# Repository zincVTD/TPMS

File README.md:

# Tire Pressure Monitoring System
Đây là mã nguồn firmware của đề tài TPMS của Võ Thành Danh. Dự án này thiết kế và phát triển một hệ thống mô phỏng hoạt động của ECU TPMS - một ECU có chức năng theo dõi tình trạng áp suất lốp xe trong các xe ô tô. Dự án thực hiện ECU TPMS trực tiếp, tức là sẽ có các cảm biến được gắn trực tiếp vào bên trong các bánh xe. Dữ liệu áp suất thu được sẽ được phát không dây ra bên ngoài và sẽ được thu bởi một bộ nhận trung tâm được đặt trong thân xe. Bộ nhận này sẽ xử lý thông tin nhận được và gửi dữ liệu ra ECU màn hình.
### Chi tiết các thành phần của dự án như sau:
- ADC_BLE: chứa mã nguồn firmware của ESP32C6 dùng để đọc giá trị cảm biến và gửi nó thông qua BLE.
- BLE_SPI: chứa mã nguồn firmware của ESP32C6 dùng để nhận dữ liệu từ BLE và gửi dữ liệu cho STM32 bằng SPI.
- TPMS: chứa mã nguồn firmware của STM32 dùng để nhận dữ liệu từ SPI và gửi nó cho ECU màn hình bằng CAN.
- Monitor: chứa mã nguồn firmware của STM32 dùng để nhận dữ liệu từ CAN và hiển thị chúng ra màn hình OLED SSD1306.\
\
**Video demo: https://youtu.be/x6ECv--hoa8**

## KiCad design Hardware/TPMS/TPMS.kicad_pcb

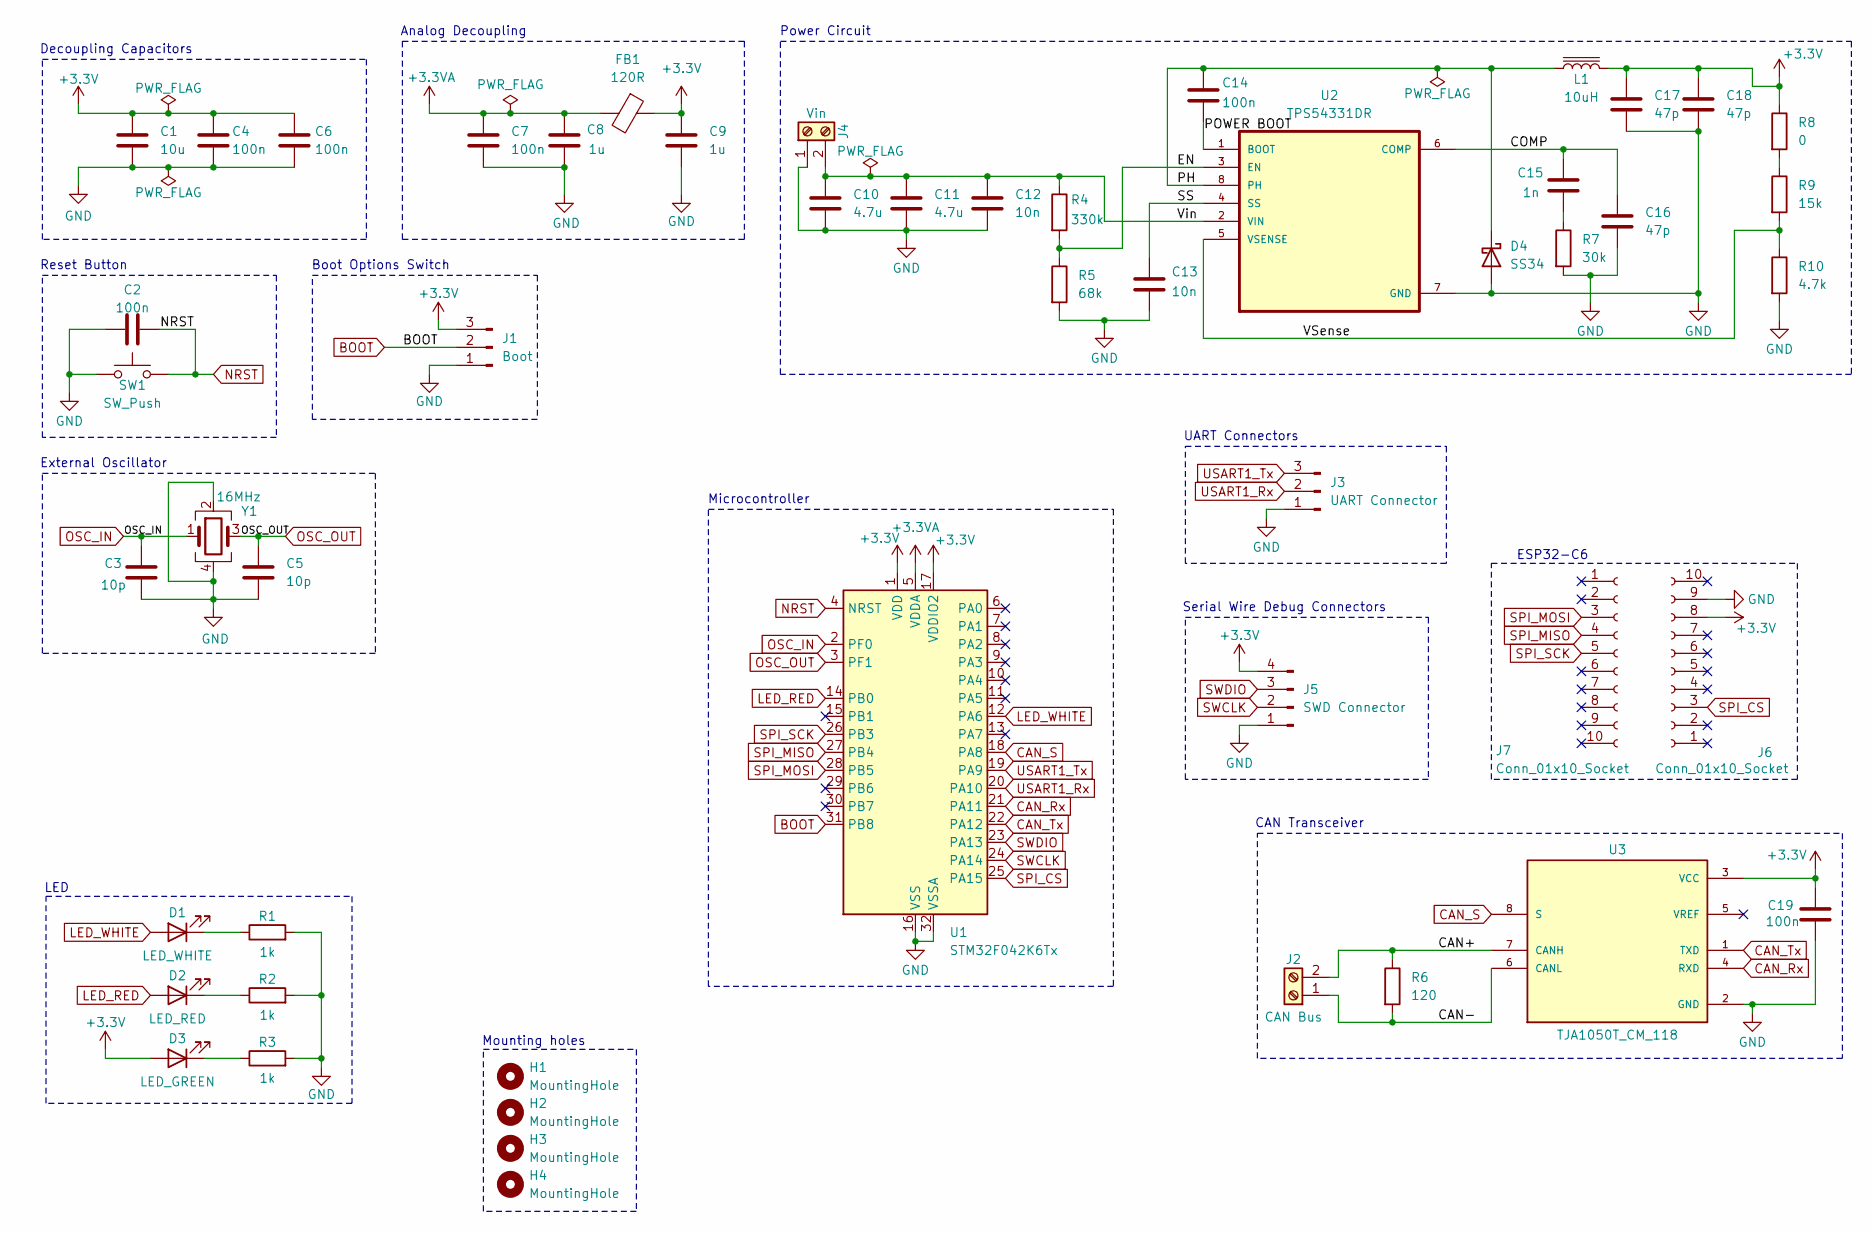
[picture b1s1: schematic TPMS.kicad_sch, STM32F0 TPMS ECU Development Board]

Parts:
C1: 10u; C_0603_1608Metric
C2, C4, C6, C7, C14, C19: 100n; C_0402_1005Metric
C3, C5: 10p; C_0402_1005Metric
C8, C9: 1u; C_0402_1005Metric
C10, C11: 4.7u; C_0603_1608Metric
C12, C13: 10n; C_0402_1005Metric
C15: 1n; C_0402_1005Metric
C16, C17, C18: 47p; C_0402_1005Metric
D1: LED_WHITE; LED_0603_1608Metric
D2: LED_RED; LED_0603_1608Metric
D3: LED_GREEN; LED_0805_2012Metric
D4: SS34; D_SMA
FB1: 120R; L_0805_2012Metric
H1, H2, H3, H4: MountingHole; MountingHole_2.5mm
J1: Boot; PinHeader_1x03_P2.54mm_Vertical
J2: CAN Bus; TerminalBlock_Phoenix_MKDS-1,5-2-5.08_1x02_P5.08mm_Horizont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
J3: UART Connector; PinHeader_1x03_P2.54mm_Vertical
J4: Vin; TerminalBlock_Phoenix_MKDS-1,5-2-5.08_1x02_P5.08mm_Horizont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
J5: SWD Connector; PinHeader_1x04_P2.54mm_Vertical
J6, J7: Conn_01x10_Socket; PinSocket_1x10_P2.54mm_Vertical
L1: 10uH; L_Sunlord_SWPA8040S
R1, R2, R3: 1k; R_0402_1005Metric
R4: 330k; R_0603_1608Metric
R5: 68k; R_0603_1608Metric
R6: 120; R_0402_1005Metric
R7: 30k; R_0603_1608Metric
R8: 0; R_0402_1005Metric
R9: 15k; R_0402_1005Metric
R10: 4.7k; R_0402_1005Metric
SW1: SW_Push; SW_SPST_TL3342
U1: STM32F042K6Tx; LQFP-32_7x7mm_P0.8mm
U2: TPS54331DR; SOIC127P599X175-8N
U3: TJA1050T_CM_118; SOIC127P600X175-8N; PARTREV 4
Y1: 16MHz; Crystal_SMD_3225-4Pin_3.2x2.5mm

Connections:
+3.3V: C1.1, C4.1, C6.1, C9.1, C17.1, C18.1, C19.1, D3.2 (A), FB1.1, J1.3, J5.4, J6.8, L1.2, R8.1, U1.1 (VDD), U1.17 (VDDIO2), U3.3 (VCC)
+3.3VA: C7.1, C8.1, FB1.2, U1.5 (VDDA)
/CAN+: J2.2, R6.1, U3.7 (CANH)
/CAN-: J2.1, R6.2, U3.6 (CANL)
/COMP: C15.1, C16.1, U2.6 (COMP)
/EN: R4.2, R5.1, U2.3 (EN)
/PH: C14.2, D4.1 (K), L1.1, U2.8 (PH)
/POWER BOOT: C14.1, U2.1 (BOOT)
/SS: C13.1, U2.4 (SS)
/VSense: R9.2, R10.1, U2.5 (VSENSE)
/Vin: C10.1, C11.1, C12.1, J4.2, R4.1, U2.2 (VIN)
BOOT: J1.2, U1.31 (PB8)
CAN_Rx: U1.21 (PA11), U3.4 (RXD)
CAN_S: U1.18 (PA8), U3.8 (S)
CAN_Tx: U1.22 (PA12), U3.1 (TXD)
GND: C1.2, C2.1, C3.2, C4.2, C5.2, C6.2, C7.2, C8.2, C9.2, C10.2, C11.2, C12.2, C13.2, C16.2, C17.2, C18.2, C19.2, D4.2 (A), J1.1, J3.1, J4.1, J5.1, J6.9, R1.2, R2.2, R3.2, R5.2, R7.2, R10.2, SW1.1, U1.16 (VSS), U1.32 (VSSA), U2.7 (GND), U3.2 (GND), Y1.2, Y1.4
LED_RED: D2.2 (A), U1.14 (PB0)
LED_WHITE: D1.2 (A), U1.12 (PA6)
NRST: C2.2, SW1.2, U1.4 (NRST)
unnamed: C15.2, R7.1
unnamed: D1.1 (K), R1.1
unnamed: D2.1 (K), R2.1
unnamed: D3.1 (K), R3.1
unnamed: R8.2, R9.1
OSC_IN: C3.1, U1.2 (PF0), Y1.1
OSC_OUT: C5.1, U1.3 (PF1), Y1.3
SPI_CS: J6.3, U1.25 (PA15)
SPI_MISO: J7.4, U1.27 (PB4)
SPI_MOSI: J7.3, U1.28 (PB5)
SPI_SCK: J7.5, U1.26 (PB3)
SWCLK: J5.2, U1.24 (PA14)
SWDIO: J5.3, U1.23 (PA13)
USART1_Rx: J3.2, U1.20 (PA10)
USART1_Tx: J3.3, U1.19 (PA9)

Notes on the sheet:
CAN Transceiver
LED
Boot Options Switch
External Oscillator
Serial Wire Debug Connectors
ESP32-C6
UART Connectors
Microcontroller
Analog Decoupling
Power Circuit
Decoupling Capacitors
Mounting holes
Reset Button

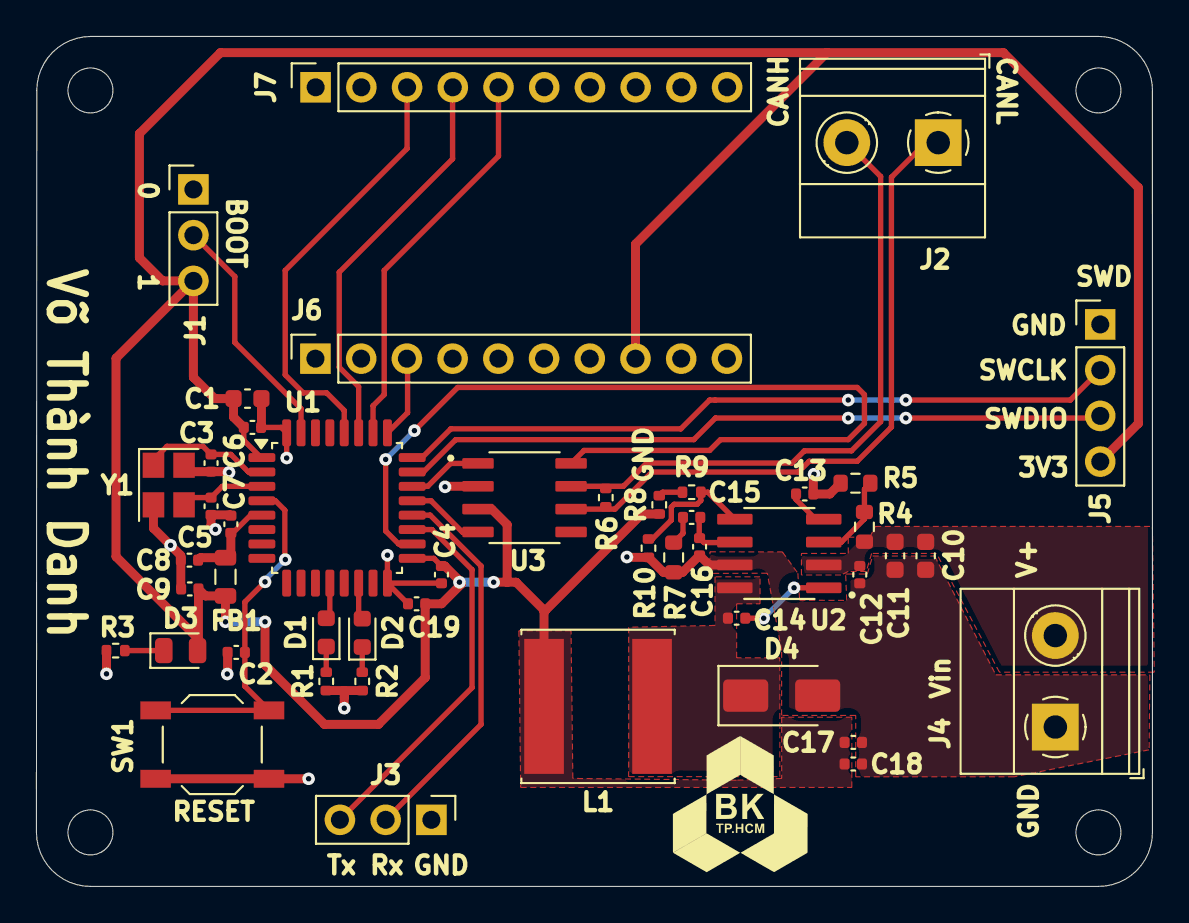
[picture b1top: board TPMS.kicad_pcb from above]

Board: 2 copper layers, 62.0 x 47.2 mm, 51 parts (0 on the bottom side), 34 nets.

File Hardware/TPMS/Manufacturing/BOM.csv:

"Reference","Value","Datasheet","Footprint","Qty","DNP"
"C1","10u","~","Capacitor_SMD:C_0603_1608Metric","1",""
"C2,C4,C6,C7,C14,C19","100n","~","Capacitor_SMD:C_0402_1005Metric","6",""
"C3,C5","10p","~","Capacitor_SMD:C_0402_1005Metric","2",""
"C8,C9","1u","~","Capacitor_SMD:C_0402_1005Metric","2",""
"C10,C11","4.7u","~","Capacitor_SMD:C_0603_1608Metric","2",""
"C12,C13","10n","~","Capacitor_SMD:C_0402_1005Metric","2",""
"C15","1n","~","Capacitor_SMD:C_0402_1005Metric","1",""
"C16,C17,C18","47p","~","Capacitor_SMD:C_0402_1005Metric","3",""
"D1","LED_WHITE","~","LED_SMD:LED_0603_1608Metric","1",""
"D2","LED_RED","~","LED_SMD:LED_0603_1608Metric","1",""
"D3","LED_GREEN","~","LED_SMD:LED_0805_2012Metric","1",""
"D4","SS34","https://www.vishay.com/docs/88751/ss32.pdf","Diode_SMD:D_SMA","1",""
"FB1","120R","~","Inductor_SMD:L_0805_2012Metric","1",""
"J1","Boot","~","Connector_PinHeader_2.54mm:PinHeader_1x03_P2.54mm_Vertical","1",""
"J2","CAN Bus","~","TerminalBlock_Phoenix:TerminalBlock_Phoenix_MKDS-1,5-2-5.08_1x02_P5.08mm_Horizontal","1",""
"J3","UART Connector","~","Connector_PinHeader_2.54mm:PinHeader_1x03_P2.54mm_Vertical","1",""
"J4","Vin","~","TerminalBlock_Phoenix:TerminalBlock_Phoenix_MKDS-1,5-2-5.08_1x02_P5.08mm_Horizontal","1",""
"J5","SWD Connector","~","Connector_PinHeader_2.54mm:PinHeader_1x04_P2.54mm_Vertical","1",""
"J6,J7","Conn_01x10_Socket","~","Connector_PinSocket_2.54mm:PinSocket_1x10_P2.54mm_Vertical","2",""
"L1","10uH","~","Inductor_SMD:L_Sunlord_SWPA8040S","1",""
"R1,R2,R3","1k","~","Resistor_SMD:R_0402_1005Metric","3",""
"R4","330k","~","Resistor_SMD:R_0603_1608Metric","1",""
"R5","68k","~","Resistor_SMD:R_0603_1608Metric","1",""
"R6","120","~","Resistor_SMD:R_0402_1005Metric","1",""
"R7","30k","~","Resistor_SMD:R_0603_1608Metric","1",""
"R8","0","~","Resistor_SMD:R_0402_1005Metric","1",""
"R9","15k","~","Resistor_SMD:R_0402_1005Metric","1",""
"R10","4.7k","~","Resistor_SMD:R_0402_1005Metric","1",""
"SW1","SW_Push","~","Button_Switch_SMD:SW_SPST_TL3342","1",""
"U1","STM32F042K6Tx","https://www.st.com/resource/en/datasheet/stm32f042k6.pdf","Package_QFP:LQFP-32_7x7mm_P0.8mm","1",""
"U2","TPS54331DR","","Package_SO:SOIC127P599X175-8N","1",""
"U3","TJA1050T_CM_118","","Package_SO:SOIC127P600X175-8N","1",""
"Y1","16MHz","~","Crystal:Crystal_SMD_3225-4Pin_3.2x2.5mm","1",""

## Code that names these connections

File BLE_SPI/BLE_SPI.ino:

#include <SPI.h>
#include <BLEDevice.h>
#include <BLEServer.h>
#include <BLEUtils.h>
#include <BLE2902.h>

// Định nghĩa BLE
#define SERVICE_UUID "4fafc201-1fb5-459e-8fcc-c5c9c331914b"
#define CHARACTERISTIC_UUID "beb5483e-36e1-4688-b7f5-ea07361b26a8"

// Định nghĩa chân SPI
#define SPI_SCK_PIN 2
#define SPI_MISO_PIN 1
#define SPI_MOSI_PIN 0
#define SPI_CS_PIN 14 // Chân CS của Slave (tương ứng FSPICS2)

// SPI settings
SPIClass *spi = NULL;
const uint32_t SPI_CLOCK = 50000;    // Tốc độ SPI 50 kHz
const uint8_t SPI_MODE = SPI_MODE0;  // CPOL = 0, CPHA = 0 (SPI_MODE0)
const uint8_t SPI_BIT_ORDER = MSBFIRST;

// Bộ đệm dữ liệu
const int BUFFER_SIZE = 6;
uint8_t tx_buffer[BUFFER_SIZE] = {0xFF, 0x00, 0x00, 0x00, 0xF0, 0xFF};
bool dataReceived = false;

// BLE setup
BLECharacteristic *pCharacteristic;
bool deviceConnected = false;

// Callback khi kết nối BLE
class MyServerCallbacks : public BLEServerCallbacks {
  void onConnect(BLEServer *pServer) {
    deviceConnected = true;
    Serial.println("Device connected");
  }

  void onDisconnect(BLEServer *pServer) {
    deviceConnected = false;
    Serial.println("Device disconnected");
  }
};

// Xử lý dữ liệu nhận được từ BLE
class MyCallbacks : public BLECharacteristicCallbacks {
  void onWrite(BLECharacteristic *pCharacteristic) {
    String value = pCharacteristic->getValue().c_str();
    if (value.length() == 2) { // Chỉ xử lý nếu nhận đúng 2 byte
      uint16_t rawADC = (value[0] << 8) | value[1]; // Kết hợp thành số 16-bit

      // Chuyển đổi giá trị từ 0-4096 sang 0-72.5
      float scaledValue = (rawADC / 4096.0) * 72.5;
      tx_buffer[0] = static_cast<uint8_t>(scaledValue); // Lưu vào byte 0 của tx_buffer

      // Cập nhật byte 4 và byte 5 theo yêu cầu
      tx_buffer[4] = 0xF0; // 4 bit đầu là 1111, 4 bit sau là 0000

      dataReceived = true;

      // Debug
      Serial.println("Data received and processed via BLE:");
      Serial.printf("Raw ADC: %u\n", rawADC);
      Serial.printf("Scaled Value: %.2f\n", scaledValue);
      Serial.print("Buffer to send: ");
      for (int i = 0; i < BUFFER_SIZE; i++) {
        Serial.printf("0x%02X ", tx_buffer[i]);
      }
      Serial.println();
    } else {
      Serial.println("Invalid data length received via BLE.");
    }
  }
};

void sendSPIData() {
  // Kích hoạt Slave (CS Low)
  digitalWrite(SPI_CS_PIN, LOW);
  delayMicroseconds(1); // Đợi Slave sẵn sàng

  // Gửi từng byte qua SPI
  for (int i = 0; i < BUFFER_SIZE; i++) {
    spi->transfer(tx_buffer[i]);
  }

  // Kết thúc truyền (CS High)
  digitalWrite(SPI_CS_PIN, HIGH);

  // Debug: In dữ liệu đã gửi
  Serial.print("Sent via SPI: ");
  for (int i = 0; i < BUFFER_SIZE; i++) {
    Serial.printf("0x%02X ", tx_buffer[i]);
  }
  Serial.println();
}

void setup() {
  // Cấu hình chân CS làm OUTPUT và đặt HIGH mặc định
  pinMode(SPI_CS_PIN, OUTPUT);
  digitalWrite(SPI_CS_PIN, HIGH);

  // Khởi tạo Serial để debug
  Serial.begin(115200);
  while (!Serial)
    ;
  Serial.println("Initializing BLE...");

  // Khởi tạo BLE
  BLEDevice::init("ESP32C6-BLE-SPI");
  BLEServer *pServer = BLEDevice::createServer();
  pServer->setCallbacks(new MyServerCallbacks());

  // Tạo Service và Characteristic
  BLEService *pService = pServer->createService(SERVICE_UUID);
  pCharacteristic = pService->createCharacteristic(
      CHARACTERISTIC_UUID,
      BLECharacteristic::PROPERTY_READ | BLECharacteristic::PROPERTY_WRITE);

  pCharacteristic->addDescriptor(new BLE2902());
  pCharacteristic->setCallbacks(new MyCallbacks());

  // Start BLE service
  pService->start();
  BLEAdvertising *pAdvertising = BLEDevice::getAdvertising();
  pAdvertising->start();
  Serial.println("BLE initialized");

  // Khởi tạo SPI
  spi = new SPIClass(FSPI);
  spi->begin(SPI_SCK_PIN, SPI_MISO_PIN, SPI_MOSI_PIN, SPI_CS_PIN);
  spi->beginTransaction(SPISettings(SPI_CLOCK, SPI_BIT_ORDER, SPI_MODE));
  Serial.println("SPI Master Initialized");
}

void loop() {
  // Gửi dữ liệu qua SPI nếu có dữ liệu BLE mới
  if (dataReceived) {
    sendSPIData();
    dataReceived = false; // Reset cờ
  }

  delay(100); // Giảm tải CPU
}

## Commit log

2024-12-26 Firmware Uploaded
2025-04-28 Update description
2025-04-29 Add more functions definition
2025-06-04 Add hardware and project report
